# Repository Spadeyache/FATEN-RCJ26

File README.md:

# RoboCupJunior Rescue Line — Robot

Key features we have. PostTrainingQuantization(PTQ) with results simulated on the K230D chip, half-duplex serial driver with 74HCT126, asymmetric PID dependent on the IMU, custom touch sensors, and an IR camera used on the hardware.

Firmware, vision, AI training pipeline, and electronics for team **FATEN**'s [RoboCupJunior Rescue Line](https://junior.robocup.org/rescue/) robot. The robot follows a line course, handles gaps, obstacles, and intersections, then enters an evacuation zone where it detects, grabs, and carries victims using an onboard YOLO(formerly MobileNet-SSD-v2-Lite) model.

**🌐 Team website:** [faten-1tdj.vercel.app](https://faten-1tdj.vercel.app/en/index.html)

<!-- TODO: add a photo of the robot here

-->

## How the robot works

One microcontroller drives the robot; two smart co-processors digest the camera data which the control loop stays fast and deterministic.

```mermaid
flowchart LR
    subgraph IN["Inputs — co-processors and sensors"]
        direction TB
        XIAO["📷 XIAO ESP32-S3<br/>camera vision:<br/>line, green, red, silver, gap"]
        K230["🧠 K230D Zero<br/>YOLOv8n victim/colour<br/>bounding boxes"]
        IMU["🧭 MPU6050 IMU"]
        TOF["📏 VL53L7CX ToF"]
        TCH["👆 Touch bumpers"]
    end
    subgraph T["Teensy 4.1 — the conductor"]
        direction TB
        RX["sensors/ — raw byte transport"]
        PROC["processing/ — decode · filter · fuse"]
        SM["state_machine/ — pick a behaviour"]
        ACT["actions/ — PID, turn, forward, arm"]
        RX --> PROC --> SM --> ACT
    end
    subgraph OUT["Outputs"]
        direction TB
        MOT["⚙️ 4× STS3032 wheels"]
        ARM["🦾 KRS arm / gripper"]
    end
    XIAO -- "UART @ 4 Mbps" --> RX
    K230 -- "UART @ 115200" --> RX
    IMU -- "I²C" --> RX
    TOF -- "I²C" --> RX
    TCH -- "GPIO" --> RX
    ACT -- "STS bus @ 1 Mbps" --> MOT
    ACT -- "ICS bus" --> ARM
```

The Teensy firmware is a 5-layer architecture (`drivers → sensors → processing → state_machine/actions`) where calls only flow downward, with one file pair per state-machine state (`LINE_Follow`, `LINE_Gap`, `LINE_Obstacle`, `EVAC_Entry`, `EVAC_SearchDeploy`, `EVAC_Exit`, …). See [teensy/STS-imuMerge/README.md](teensy/STS-imuMerge/README.md) and the interactive [system map](Docs/architecture.html) for the full picture.

## Hardware

| Part | Role |
|---|---|
| Teensy 4.1 | Main controller: sensor fusion, state machine, motion control |
| Seeed XIAO ESP32-S3 Sense | Line-camera co-processor: line position, green/red markers, silver tape, gap detection |
| Sipeed CanMV K230D Zero | AI co-processor: YOLOv8n victim / colour detection (kmodel via nncase) |
| MPU6050 | IMU — pitch / roll / yaw |
| Pololu VL53L7CX | Multizone ToF — walls and obstacle distance |
| 4× Feetech STS3032 | Serial-bus wheel servos (1 Mbps) |
| Kondo KRS servos & Hitech HS45HB | Victim arm and grippers |
| Custom PCBs (EasyEDA) | Power distribution, adapters, breakouts — see [electronics/](electronics/) |

The custom PCBs form a stacked electronics module. The map below shows how the boards connect:

## Repository layout

| Directory | Contents |
|---|---|
| [teensy/](teensy/) | Teensy 4.1 firmware. **`STS-imuMerge/` is the competition firmware**; other folders are hardware bring-up tests (IMU, STS servos, touch) |
| [xiaoesp/](xiaoesp/) | XIAO ESP32-S3 camera firmware (`XIAOdev/`) + Web Serial debug viewer (`esp32_camera_viewer.html`) |
| [k230-final-train/](k230-final-train/) | **Current** YOLOv8n training pipeline: dataset → train → ONNX → kmodel → simulate → compare → deploy, all in Docker, one script per step |
| [k230-inference/](k230-inference/) | MicroPython code that runs on the K230D (CanMV): live detection, UART protocol to the Teensy |
| [k230/](k230/) | Legacy training pipeline + datasets (superseded by `k230-final-train/`) |
| [electronics/](electronics/) | EasyEDA projects, 3D exports, KiCad archive |
| [Docs/](Docs/) | Interactive HTML docs — open in a browser (see below) |
| [dev-tools/](dev-tools/) | Flashing images, servo manager, drivers, terminal tools |

## Documentation

The `Docs/` folder holds self-contained HTML documents (open locally in any browser):

- [architecture.html](Docs/architecture.html) — full system map: co-processors, 5-layer firmware, state machine, PID
- [APIs.html](Docs/APIs.html) — inter-board protocols and APIs
- [mapping-overview.html](Docs/mapping-overview.html) — mapping / pose overview
- [hardware530_design_upgrade.html](Docs/hardware530_design_upgrade.html), [hardware530_parts_upgrade.html](Docs/hardware530_parts_upgrade.html) — hardware upgrade notes
- [k526_PTQ_model_compare.html](Docs/k526_PTQ_model_compare.html) — kmodel post-training-quantization comparison

Each firmware layer also documents itself: every `src/<layer>/` folder has its own `README.md` with that layer's rules.

## Building and running

### Teensy firmware

Requires [Teensyduino](https://www.pjrc.com/teensy/teensyduino.html) (Arduino IDE or `arduino-cli` with the `teensy:avr` core):

```powershell
cd teensy/STS-imuMerge
arduino-cli compile --fqbn "teensy:avr:teensy41:usb=serial,speed=600,opt=o2std,keys=en-us" --build-path build .
```

### XIAO camera firmware

Build profile is pinned in [sketch.yaml](xiaoesp/XIAOdev/sketch.yaml) (esp32 core 3.3.7):

```powershell
cd xiaoesp/XIAOdev
arduino-cli compile --profile xiaoesp32s3
```

### K230D AI co-processor

1. Flash the CanMV MicroPython image (`CanMV_K230D_Zero_micropython_v1.5-legacy … nncase_v2.9.0`, in [dev-tools/](dev-tools/)) — see [k230-inference/README.md](k230-inference/README.md)
2. Copy the contents of [k230-inference/](k230-inference/) plus your `.kmodel` to the device SD card

### Training a new model

Fully reproducible in Docker — annotated dataset in, deployable `.kmodel` out:

```powershell
cd k230-final-train
.\competition_run.ps1 -Name victim_v2 -Epochs 100
```

See [k230-final-train/README.md](k230-final-train/README.md) for the step-by-step scripts and the PTQ search/compare workflow. Note: kmodels must be converted with **nncase 2.9.0-compatible tooling** to match the flashed CanMV firmware.

## Acknowledgements

### Sponsors

Team FATEN thanks the sponsors who made this robot possible:

<p>
  &nbsp;&nbsp;&nbsp;
  &nbsp;&nbsp;&nbsp;
  &nbsp;&nbsp;&nbsp;
  &nbsp;&nbsp;&nbsp;
  
</p>

- **[EasyEDA](https://easyeda.com/) & [JLCPCB](https://jlcpcb.com/)** — provided the PCB design software and board fabrication credit; the integrated design-to-manufacture workflow carried our boards smoothly from schematic to delivered PCB.
- **[Keeppower](https://keeppower.com/)** — supplied high-spec protected batteries, with the protection circuit custom-designed for our robot, and covered most of the battery and shipping costs.
- **[Hitec](https://hitecrcd.com/)** — provided motors for the robot arm along with battery chargers and maintenance jigs; their high-spec LiFePO4 balance charger kept our batteries reliably charged throughout the competition.
- **[Pololu](https://www.pololu.com/)** — supported the team's sensor hardware, including the VL53L7CX multizone time-of-flight sensor the robot uses for wall and obstacle detection.

More photos from the competition are in our [Google Drive folder](https://drive.google.com/drive/folders/1ek6edaTA_Ugfu6BttLYHi5sbRvwh5g2C).

### Institutions

Our team members represent:

<p>
  &nbsp;&nbsp;&nbsp;
  &nbsp;&nbsp;&nbsp;
  
</p>

### Open source

This robot builds on Ultralytics YOLOv8, nncase, CanMV, Teensyduino, and the Arduino ESP32 core.

## License

This project is licensed under the **Creative Commons Attribution-NonCommercial 4.0 International License (CC BY-NC 4.0)** see [LICENSE](LICENSE) for details.

In short: you're welcome to study this project, learn from it, and build your own work on top of it, as long as you credit team FATEN (a link back to this repository) and don't use it for commercial purposes. Please don't just lift the code wholesale.

Third-party components (YOLOv8, nncase, CanMV, Teensyduino, the Arduino ESP32 core, etc.) remain under their own licenses.

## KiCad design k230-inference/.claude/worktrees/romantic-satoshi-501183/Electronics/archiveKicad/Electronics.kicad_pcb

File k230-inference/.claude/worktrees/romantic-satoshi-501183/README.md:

/CanMV... for k230d zero development

/k230dev-yolo...enviroment to train a yolov8n model and convert to a .kmodel for k230

/teensydev... teensy4.1 developments

/xiaoesp32dev...all developments for xiao

/Electronics... all electronics development - We use EasyEDA as our main ecad software

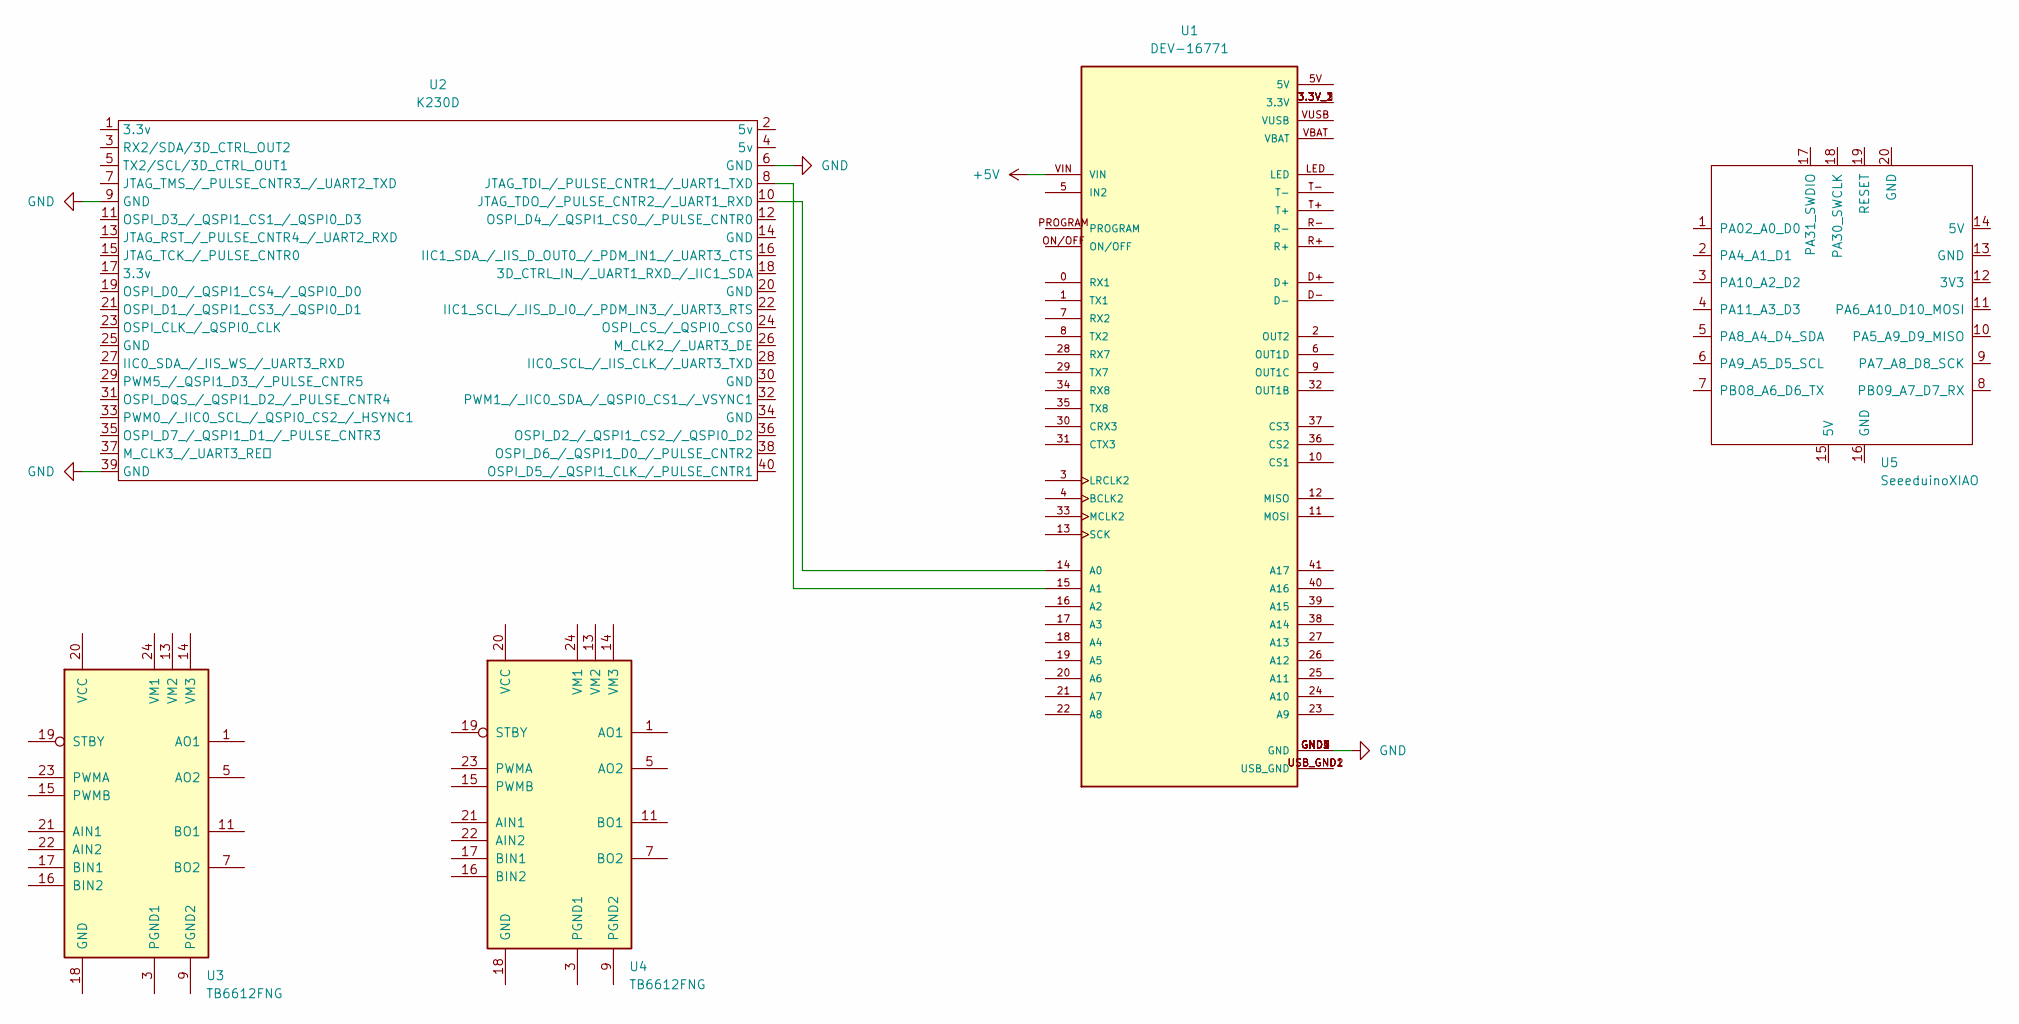
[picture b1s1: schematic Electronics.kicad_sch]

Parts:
U1: DEV-16771; MODULE_DEV-16771; PARTREV 4.1
U2: K230D; PinSocket_2x20_P2.54mm_Vertical_SMD
U3, U4: TB6612FNG; SSOP-24_5.3x8.2mm_P0.65mm
U5: SeeeduinoXIAO; MCU_Seeed_ESP32C3

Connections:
+5V: U1.VIN
GND: U1.GND1 (GND), U1.GND2 (GND), U1.GND3 (GND), U1.GND4 (GND), U1.GND5 (GND), U2.6 (GND), U2.9 (GND), U2.39 (GND)
unnamed: U1.3.3V_1 (3.3V), U1.3.3V_2 (3.3V), U1.3.3V_3 (3.3V)
unnamed: U1.14 (A0), U2.10 (JTAG_TDO_/_PULSE_CNTR2_/_UART1_RXD)
unnamed: U1.15 (A1), U2.8 (JTAG_TDI_/_PULSE_CNTR1_/_UART1_TXD)
unnamed: U1.USB_GND1 (USB_GND), U1.USB_GND2 (USB_GND)
unnamed: U3.1 (AO1), U3.2 (AO1)
unnamed: U3.5 (AO2), U3.6 (AO2)
unnamed: U3.11 (BO1), U3.12 (BO1)
unnamed: U3.7 (BO2), U3.8 (BO2)
unnamed: U3.3 (PGND1), U3.4 (PGND1)
unnamed: U3.9 (PGND2), U3.10 (PGND2)
unnamed: U4.1 (AO1), U4.2 (AO1)
unnamed: U4.5 (AO2), U4.6 (AO2)
unnamed: U4.11 (BO1), U4.12 (BO1)
unnamed: U4.7 (BO2), U4.8 (BO2)
unnamed: U4.3 (PGND1), U4.4 (PGND1)
unnamed: U4.9 (PGND2), U4.10 (PGND2)

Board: 2 copper layers, 5 parts (0 on the bottom side), 17 nets, no tracks yet.

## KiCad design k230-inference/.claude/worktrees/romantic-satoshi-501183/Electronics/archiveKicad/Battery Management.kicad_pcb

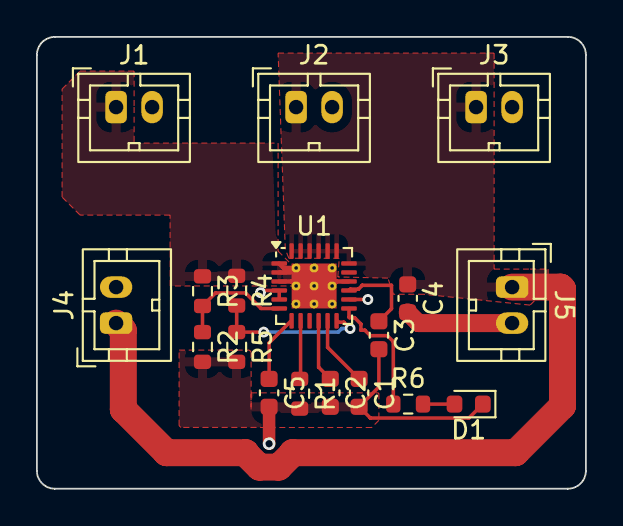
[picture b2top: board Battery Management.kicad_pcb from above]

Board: 2 copper layers, 30.5 x 25.1 mm, 18 parts (0 on the bottom side), 12 nets.

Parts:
C1: 330pF; C_0603_1608Metric
C2: 128pF; C_0603_1608Metric
C3: 2.2nF; C_0603_1608Metric
C4: 470nF; C_0603_1608Metric
C5: 22nF; C_0603_1608Metric
D1: LED; D_0603_1608Metric
J1, J2, J3, J4, J5: Conn_01x02; TE_440054-2_1x02_P2.00mm_Vertical
R1: 148; R_0603_1608Metric
R2: 225k; R_0603_1608Metric
R3, R4: 1M; R_0603_1608Metric
R5: 2k; R_0603_1608Metric
R6: 10K; R_0603_1608Metric
U1: TSP25983; VQFN-24-1EP_4x4mm_P0.5mm_EP2.5x2.5mm_ThermalVias

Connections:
+6.6V: C4.1, J2.1, J3.1, J4.1, J5.1, U1.17 (OUT_2), U1.18 (OUT_3), U1.19 (OUT_4), U1.20 (OUT_5), U1.21 (OUT_6), U1.22 (OUT_7), U1.23 (OUT_8), U1.24 (OUT)
+BATT: J1.1, R3.1, R4.1, U1.1 (IN_2), U1.2 (IN_3), U1.3 (IN_4), U1.16 (IN_5), U1.25 (IN)
GND: C1.2, C2.2, C3.2, C4.2, C5.2, D1.1 (K), J1.2, J2.2, J3.2, J4.2, J5.2, R1.2, R2.2, R5.2, U1.4 (GND_2), U1.5 (GND_3), U1.14 (GND_4)
unnamed: D1.2 (A), R6.2
unnamed: C3.1, U1.15 (DV/DT_BGATE)
unnamed: R2.1, R3.2, U1.6 (EN/UVLO)
unnamed: R1.1, U1.8 (ILIM)
unnamed: C5.1, U1.7 (ITIMER)
unnamed: C1.1, U1.11 (NRETRY)
unnamed: R4.2, R5.1, U1.12 (OVLO)
unnamed: R6.1, U1.13 (PG)
unnamed: C2.1, U1.10 (RETRY_DLY)

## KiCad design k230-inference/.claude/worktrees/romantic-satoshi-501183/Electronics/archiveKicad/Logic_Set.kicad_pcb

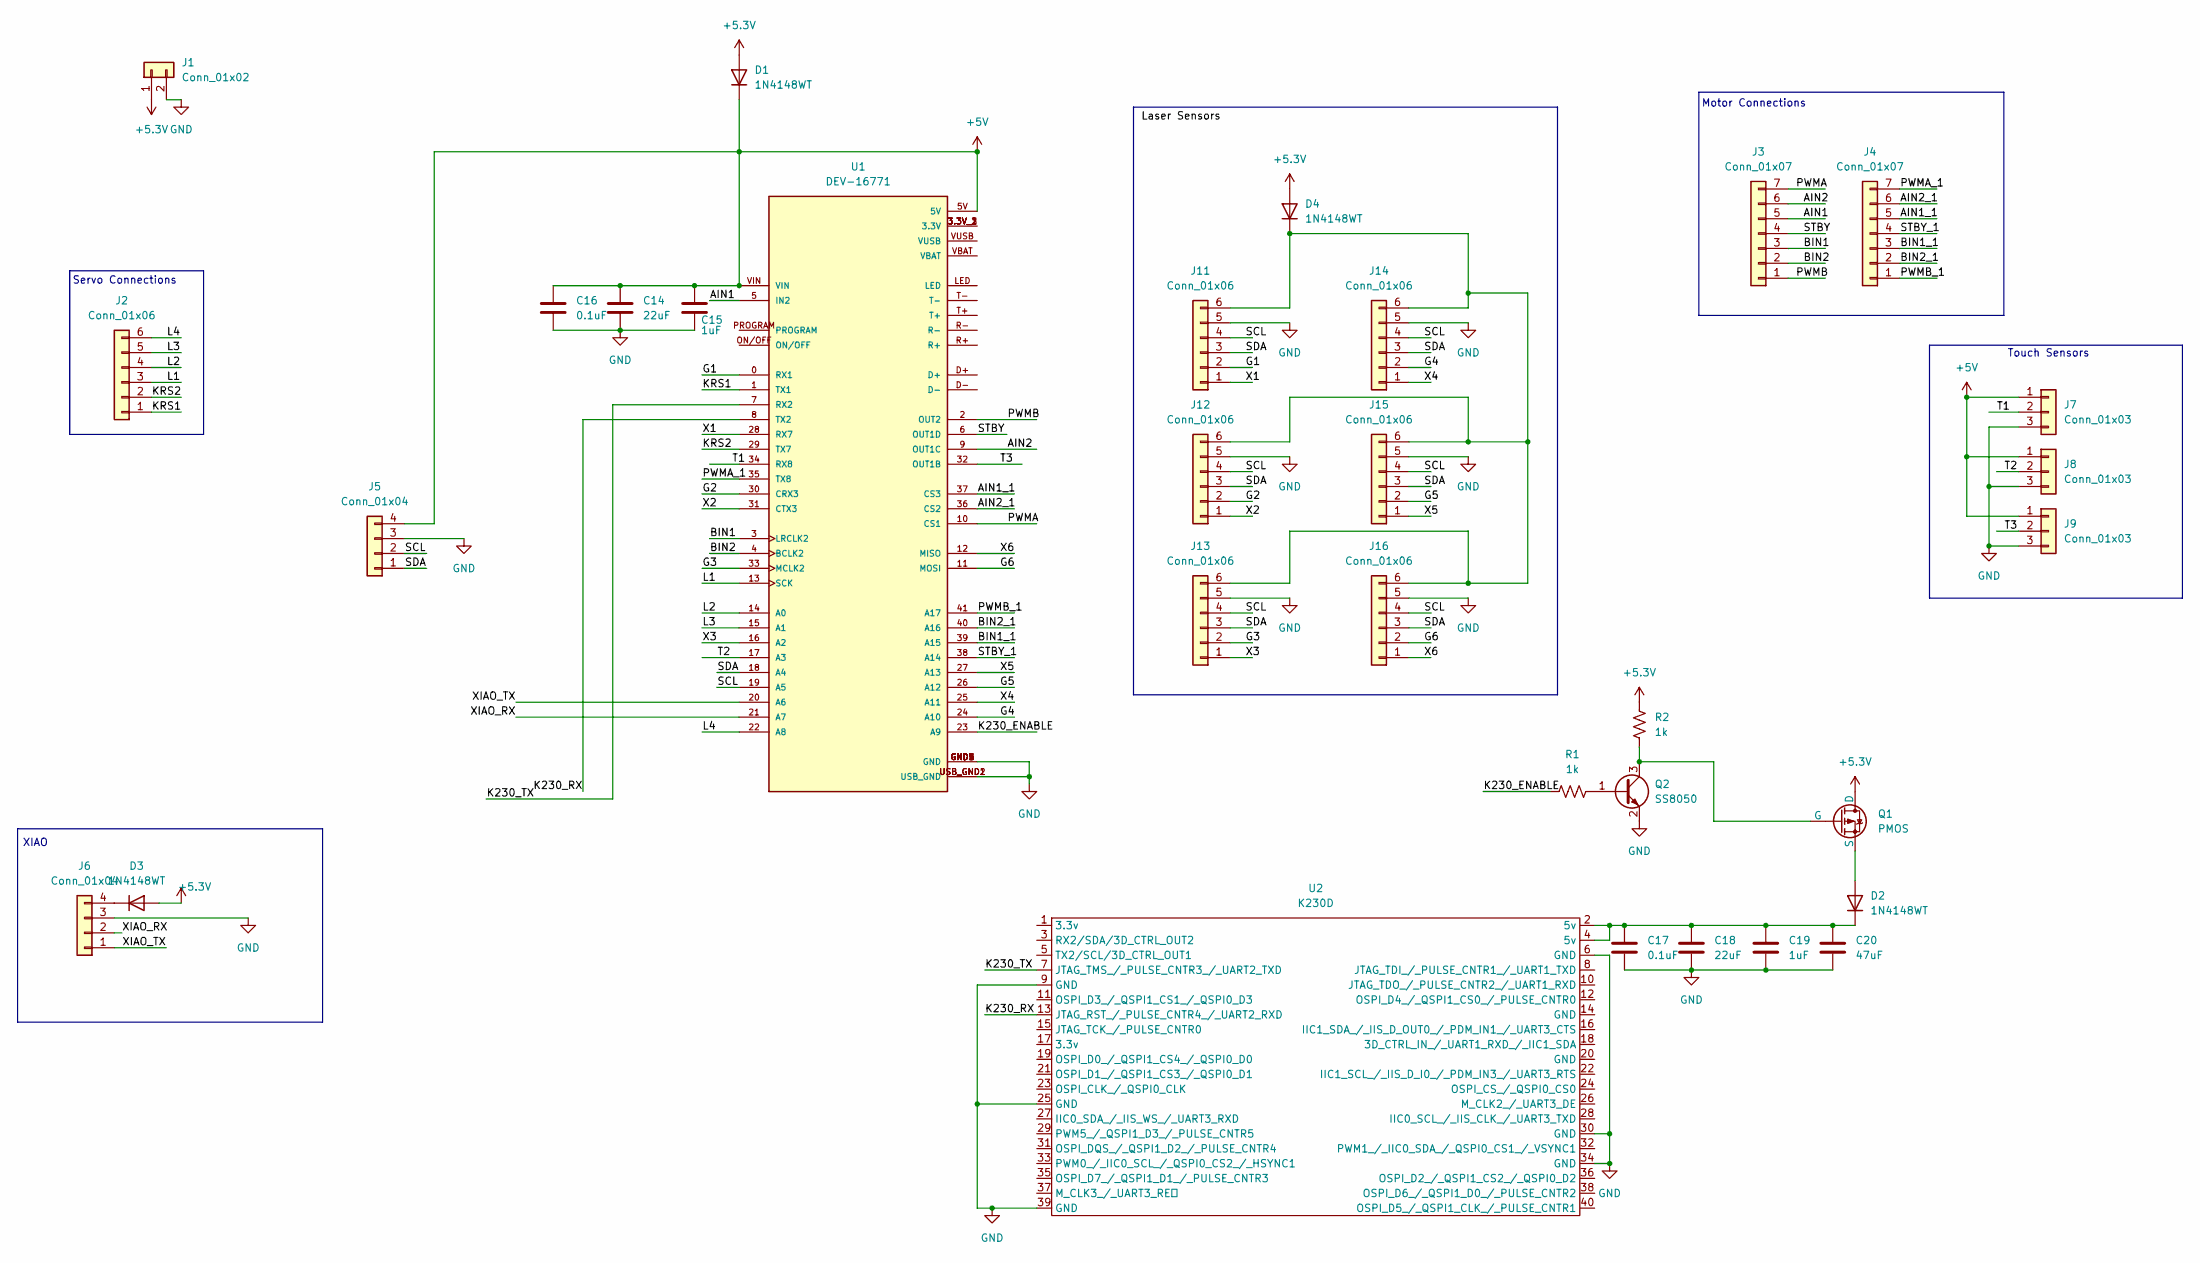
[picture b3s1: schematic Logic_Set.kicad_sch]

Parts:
C14, C18: 22uF; C_0603_1608Metric
C15, C19: 1uF; C_0603_1608Metric
C16, C17: 0.1uF; C_0603_1608Metric
C20: 47uF; C_0603_1608Metric
D1, D2, D3, D4: 1N4148WT; D_SOD-523
J1: Conn_01x02; Molex_KK-396_5273-02A_1x02_P3.96mm_Vertical
J2, J11, J12, J13, J14, J15, J16: Conn_01x06; JST_EH_B6B-EH-A_1x06_P2.50mm_Vertical
J3, J4: Conn_01x07; JST_EH_B7B-EH-A_1x07_P2.50mm_Vertical
J5, J6: Conn_01x04; JST_EH_B4B-EH-A_1x04_P2.50mm_Vertical
J7, J8, J9: Conn_01x03; JST_EH_B3B-EH-A_1x03_P2.50mm_Vertical
Q1: PMOS; SOT-23
Q2: SS8050; SOT-23
R1, R2: 1k; R_0603_1608Metric
U1: DEV-16771; Teensy4.1; PARTREV 4.1
U2: K230D; PinSocket_2x20_P2.54mm_Vertical_SMD

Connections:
+5.3V: D1.2 (A), D3.2 (A), D4.2 (A), J1.1, Q1.1 (D), R2.1
+5V: C14.1, C15.1, C16.1, D1.1 (K), J5.4, J7.1, J8.1, J9.1, U1.5V, U1.VIN
/AIN1: J3.5, U1.5 (IN2)
/AIN1_1: J4.5, U1.37 (CS3)
/AIN2: J3.6, U1.9 (OUT1C)
/AIN2_1: J4.6, U1.36 (CS2)
/BIN1: J3.3, U1.3 (LRCLK2)
/BIN1_1: J4.3, U1.39 (A15)
/BIN2: J3.2, U1.4 (BCLK2)
/BIN2_1: J4.2, U1.40 (A16)
/G1: J11.2, U1.0 (RX1)
/G2: J12.2, U1.30 (CRX3)
/G3: J13.2, U1.33 (MCLK2)
/G4: J14.2, U1.24 (A10)
/G5: J15.2, U1.26 (A12)
/G6: J16.2, U1.11 (MOSI)
/K230_ENABLE: R1.1, U1.23 (A9)
/K230_RX: U1.8 (TX2), U2.13 (JTAG_RST_/_PULSE_CNTR4_/_UART2_RXD)
/K230_TX: U1.7 (RX2), U2.7 (JTAG_TMS_/_PULSE_CNTR3_/_UART2_TXD)
/KRS1: J2.1, U1.1 (TX1)
/KRS2: J2.2, U1.29 (TX7)
/L1: J2.3, U1.13 (SCK)
/L2: J2.4, U1.14 (A0)
/L3: J2.5, U1.15 (A1)
/L4: J2.6, U1.22 (A8)
/PWMA: J3.7, U1.10 (CS1)
/PWMA_1: J4.7, U1.35 (TX8)
/PWMB: J3.1, U1.2 (OUT2)
/PWMB_1: J4.1, U1.41 (A17)
/SCL: J5.2, J11.4, J12.4, J13.4, J14.4, J15.4, J16.4, U1.19 (A5)
/SDA: J5.1, J11.3, J12.3, J13.3, J14.3, J15.3, J16.3, U1.18 (A4)
/STBY: J3.4, U1.6 (OUT1D)
/STBY_1: J4.4, U1.38 (A14)
/T1: J7.2, U1.34 (RX8)
/T2: J8.2, U1.17 (A3)
/T3: J9.2, U1.32 (OUT1B)
/X1: J11.1, U1.28 (RX7)
/X2: J12.1, U1.31 (CTX3)
/X3: J13.1, U1.16 (A2)
/X4: J14.1, U1.25 (A11)
/X5: J15.1, U1.27 (A13)
/X6: J16.1, U1.12 (MISO)
/XIAO_RX: J6.2, U1.21 (A7)
/XIAO_TX: J6.1, U1.20 (A6)
GND: C14.2, C15.2, C16.2, C17.2, C18.2, C19.2, C20.2, J1.2, J5.3, J6.3, J7.3, J8.3, J9.3, J11.5, J12.5, J13.5, J14.5, J15.5, J16.5, Q2.2 (E), U1.GND1 (GND), U1.GND2 (GND), U1.GND3 (GND), U1.GND4 (GND), U1.GND5 (GND), U1.USB_GND1 (USB_GND), U1.USB_GND2 (USB_GND), U2.6 (GND), U2.9 (GND), U2.25 (GND), U2.30 (GND), U2.34 (GND), U2.39 (GND)
unnamed: D2.2 (A), Q1.3 (S)
unnamed: C17.1, C18.1, C19.1, C20.1, D2.1 (K), U2.2 (5v), U2.4 (5v)
unnamed: D3.1 (K), J6.4
unnamed: D4.1 (K), J11.6, J12.6, J13.6, J14.6, J15.6, J16.6
unnamed: Q1.2 (G), Q2.3 (C), R2.2
unnamed: Q2.1 (B), R1.2
unnamed: U1.3.3V_1 (3.3V), U1.3.3V_2 (3.3V), U1.3.3V_3 (3.3V)

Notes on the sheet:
Motor Connections
Servo Connections
XIAO
Touch Sensors

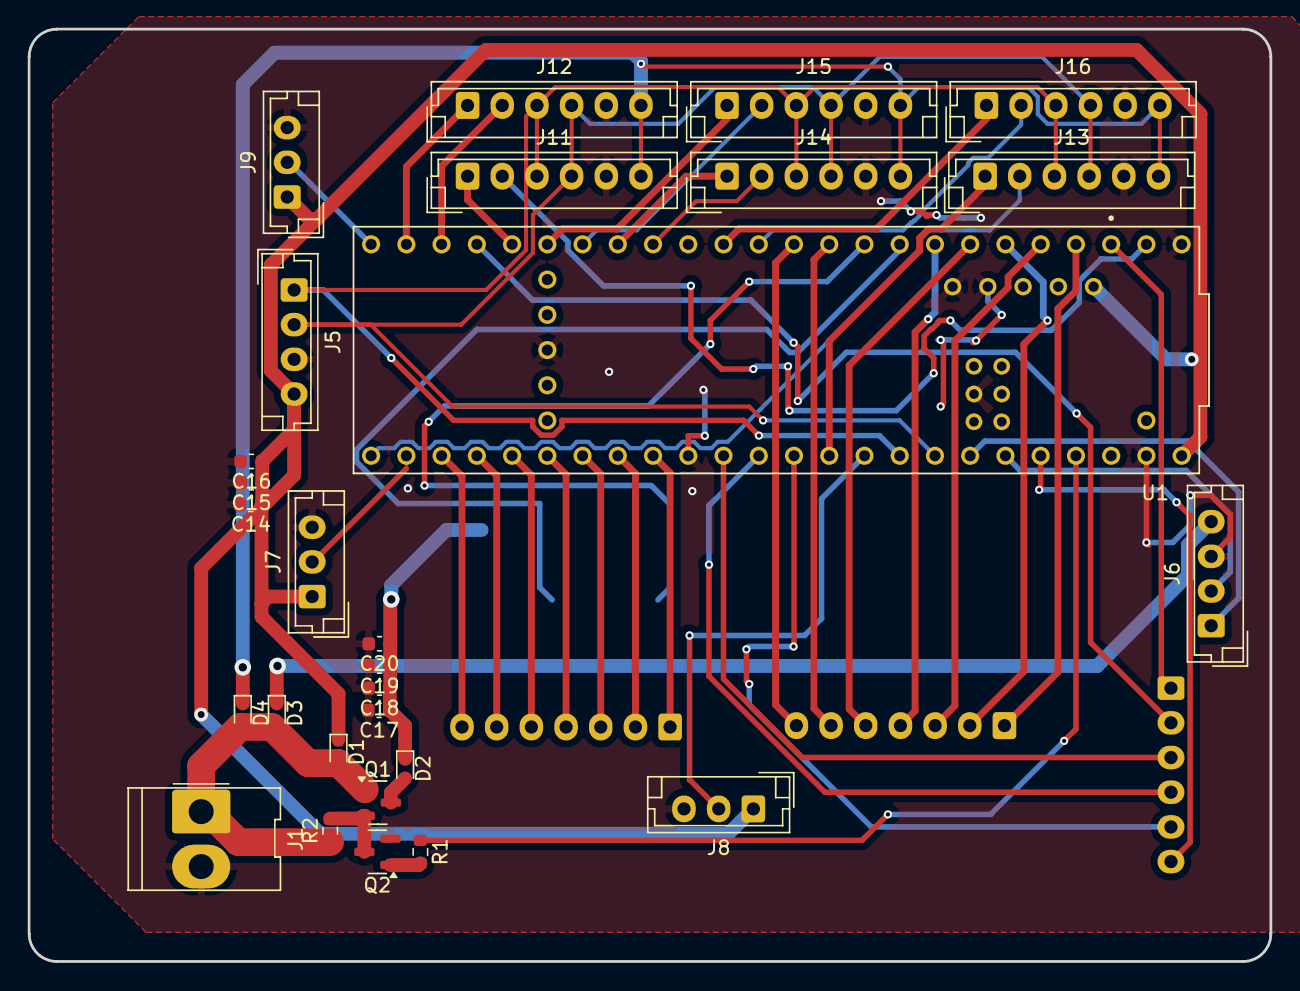
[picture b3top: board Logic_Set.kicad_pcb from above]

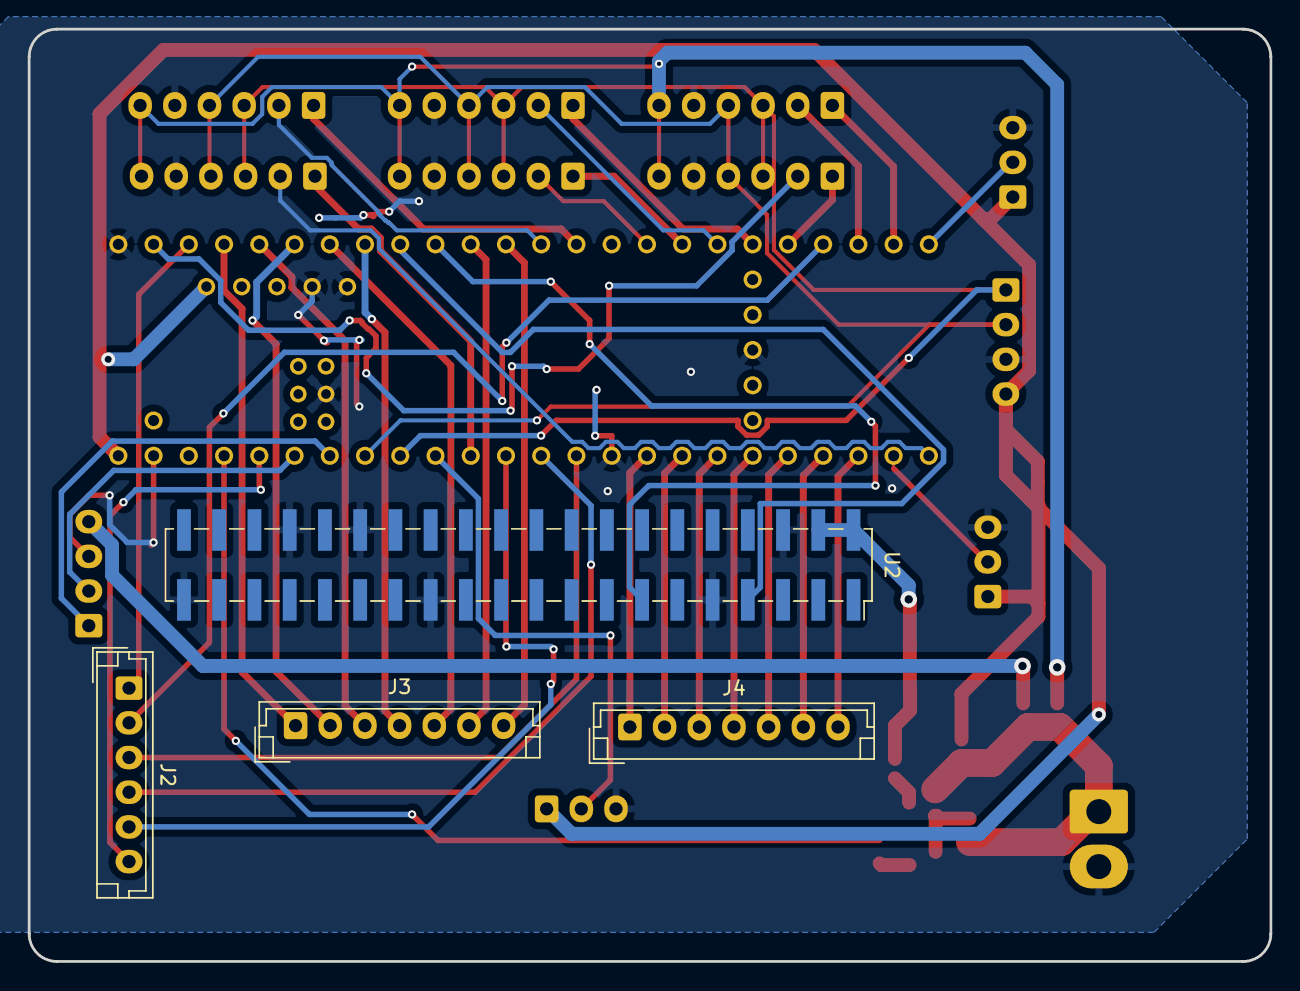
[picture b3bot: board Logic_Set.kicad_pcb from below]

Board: 2 copper layers, 89.5 x 67.2 mm, 32 parts (4 on the bottom side), 52 nets.

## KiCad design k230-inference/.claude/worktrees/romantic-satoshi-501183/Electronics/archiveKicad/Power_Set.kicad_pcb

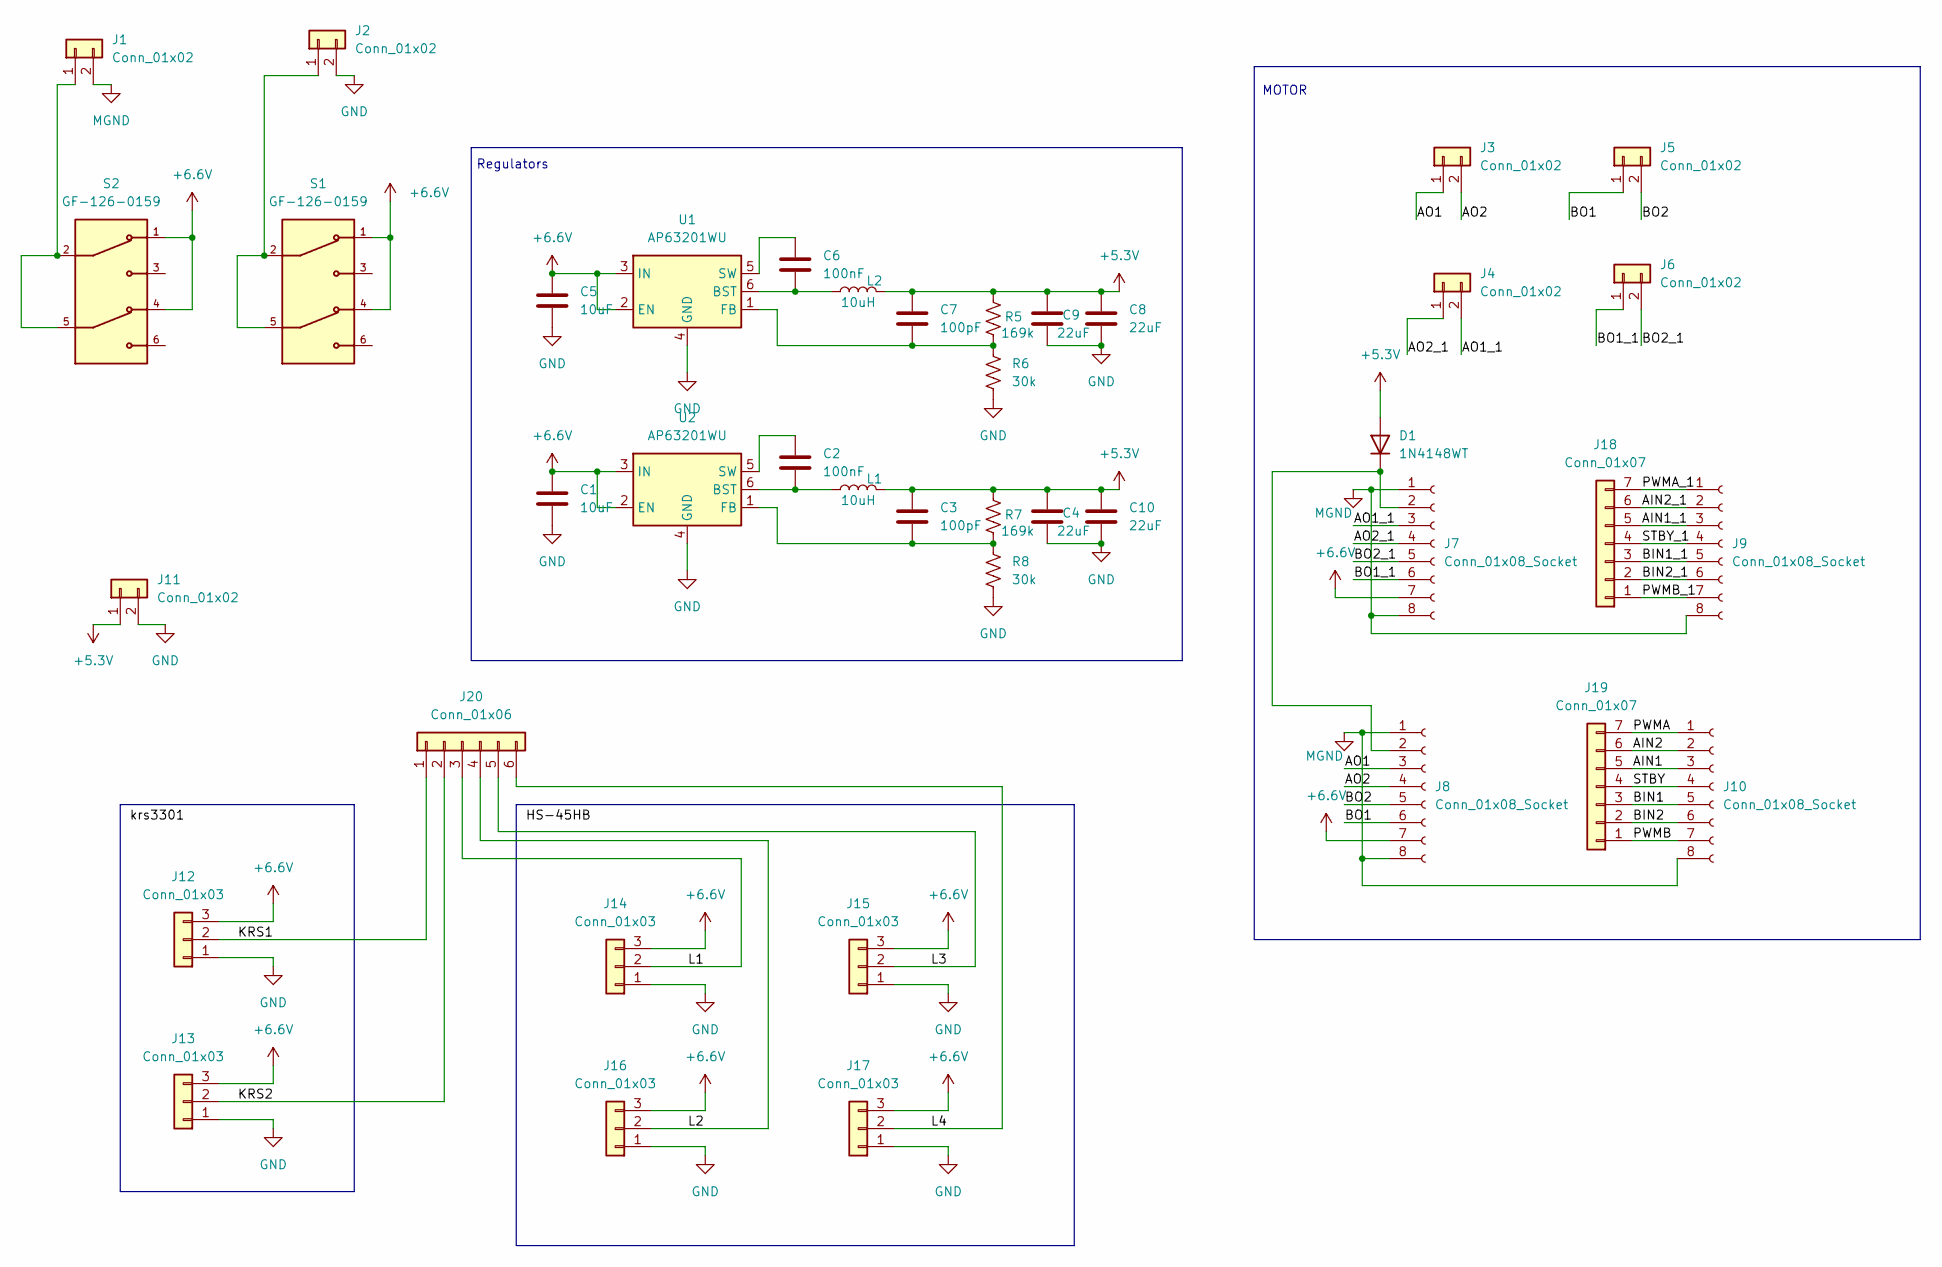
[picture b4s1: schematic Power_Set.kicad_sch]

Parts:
C1, C5: 10uF; C_0603_1608Metric
C2, C6: 100nF; C_0603_1608Metric
C3, C7: 100pF; C_0603_1608Metric
C4, C8, C9, C10: 22uF; C_0603_1608Metric
D1: 1N4148WT; D_SOD-523
J1, J2, J3, J4, J5, J6, J11: Conn_01x02; Molex_KK-396_A-41791-0002_1x02_P3.96mm_Vertical
J7, J8, J9, J10: Conn_01x08_Socket; PinHeader_1x08_P2.54mm_Vertical
J12, J13, J14, J15, J16, J17: Conn_01x03; JST_EH_B3B-EH-A_1x03_P2.50mm_Vertical
J18, J19: Conn_01x07; JST_EH_B7B-EH-A_1x07_P2.50mm_Vertical
J20: Conn_01x06; JST_EH_B6B-EH-A_1x06_P2.50mm_Vertical
L1, L2: 10uH; L_1210_3225Metric
R5, R7: 169k; R_0603_1608Metric
R6, R8: 30k; R_0603_1608Metric
S1, S2: GF-126-0159; SW_GF-126-0159
U1, U2: AP63201WU; TSOT-23-6

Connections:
+5.3V: C3.1, C4.1, C7.1, C8.1, C9.1, C10.1, D1.2 (A), J11.1, L1.2, L2.2, R5.1, R7.1
+6.6V: C1.1, C5.1, J7.7, J8.7, J12.3, J13.3, J14.3, J15.3, J16.3, J17.3, S1.1, S1.4, S2.1, S2.4, U1.2 (EN), U1.3 (IN), U2.2 (EN), U2.3 (IN)
/AIN1: J10.3, J19.5
/AIN1_1: J9.3, J18.5
/AIN2: J10.2, J19.6
/AIN2_1: J9.2, J18.6
/AO1: J3.1, J8.3
/AO1_1: J4.2, J7.3
/AO2: J3.2, J8.4
/AO2_1: J4.1, J7.4
/BIN1: J10.5, J19.3
/BIN1_1: J9.5, J18.3
/BIN2: J10.6, J19.2
/BIN2_1: J9.6, J18.2
/BO1: J5.1, J8.6
/BO1_1: J6.1, J7.6
/BO2: J5.2, J8.5
/BO2_1: J6.2, J7.5
/KRS1: J12.2, J20.1
/KRS2: J13.2, J20.2
/L1: J14.2, J20.3
/L2: J16.2, J20.4
/L3: J15.2, J20.5
/L4: J17.2, J20.6
/PWMA: J10.1, J19.7
/PWMA_1: J9.1, J18.7
/PWMB: J10.7, J19.1
/PWMB_1: J9.7, J18.1
/STBY: J10.4, J19.4
/STBY_1: J9.4, J18.4
GND: C1.2, C4.2, C5.2, C8.2, C9.2, C10.2, J2.2, J11.2, J12.1, J13.1, J14.1, J15.1, J16.1, J17.1, R6.2, R8.2, U1.4 (GND), U2.4 (GND)
MGND: J1.2, J7.1, J7.8, J8.1, J8.8, J9.8, J10.8
unnamed: D1.1 (K), J7.2, J8.2
unnamed: J1.1, S2.2, S2.5
unnamed: J2.1, S1.2, S1.5
unnamed: C6.2, L2.1, U1.6 (BST)
unnamed: C7.2, R5.2, R6.1, U1.1 (FB)
unnamed: C6.1, U1.5 (SW)
unnamed: C2.2, L1.1, U2.6 (BST)
unnamed: C3.2, R7.2, R8.1, U2.1 (FB)
unnamed: C2.1, U2.5 (SW)

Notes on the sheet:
Regulators
MOTOR

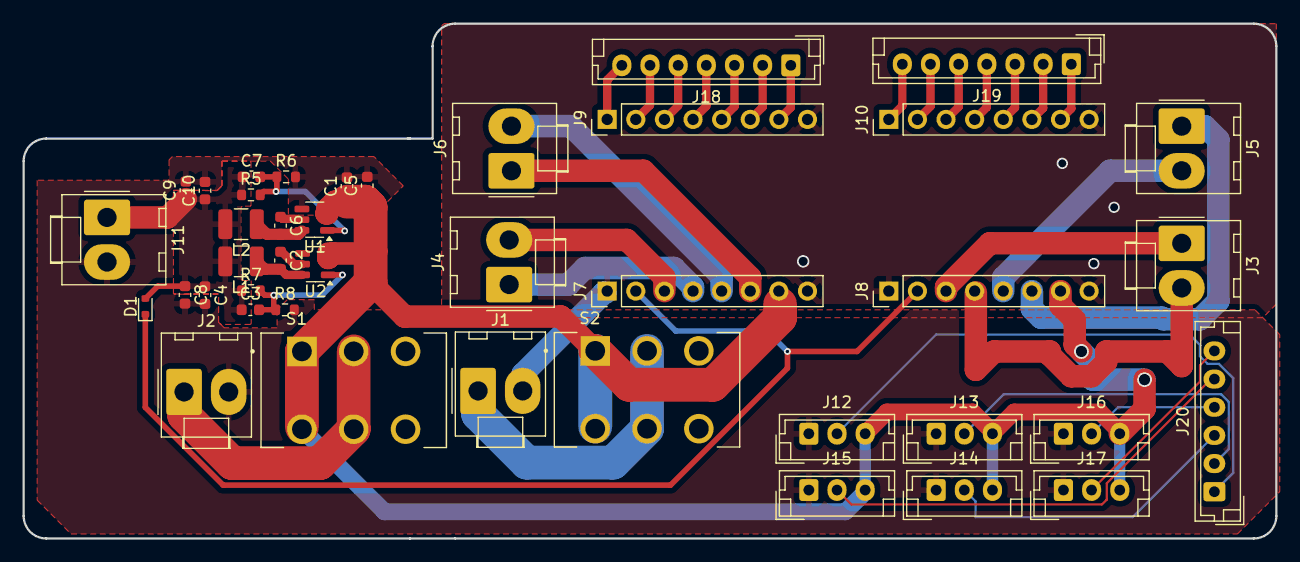
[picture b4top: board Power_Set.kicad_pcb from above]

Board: 2 copper layers, 111.2 x 45.7 mm, 41 parts (0 on the bottom side), 41 nets.

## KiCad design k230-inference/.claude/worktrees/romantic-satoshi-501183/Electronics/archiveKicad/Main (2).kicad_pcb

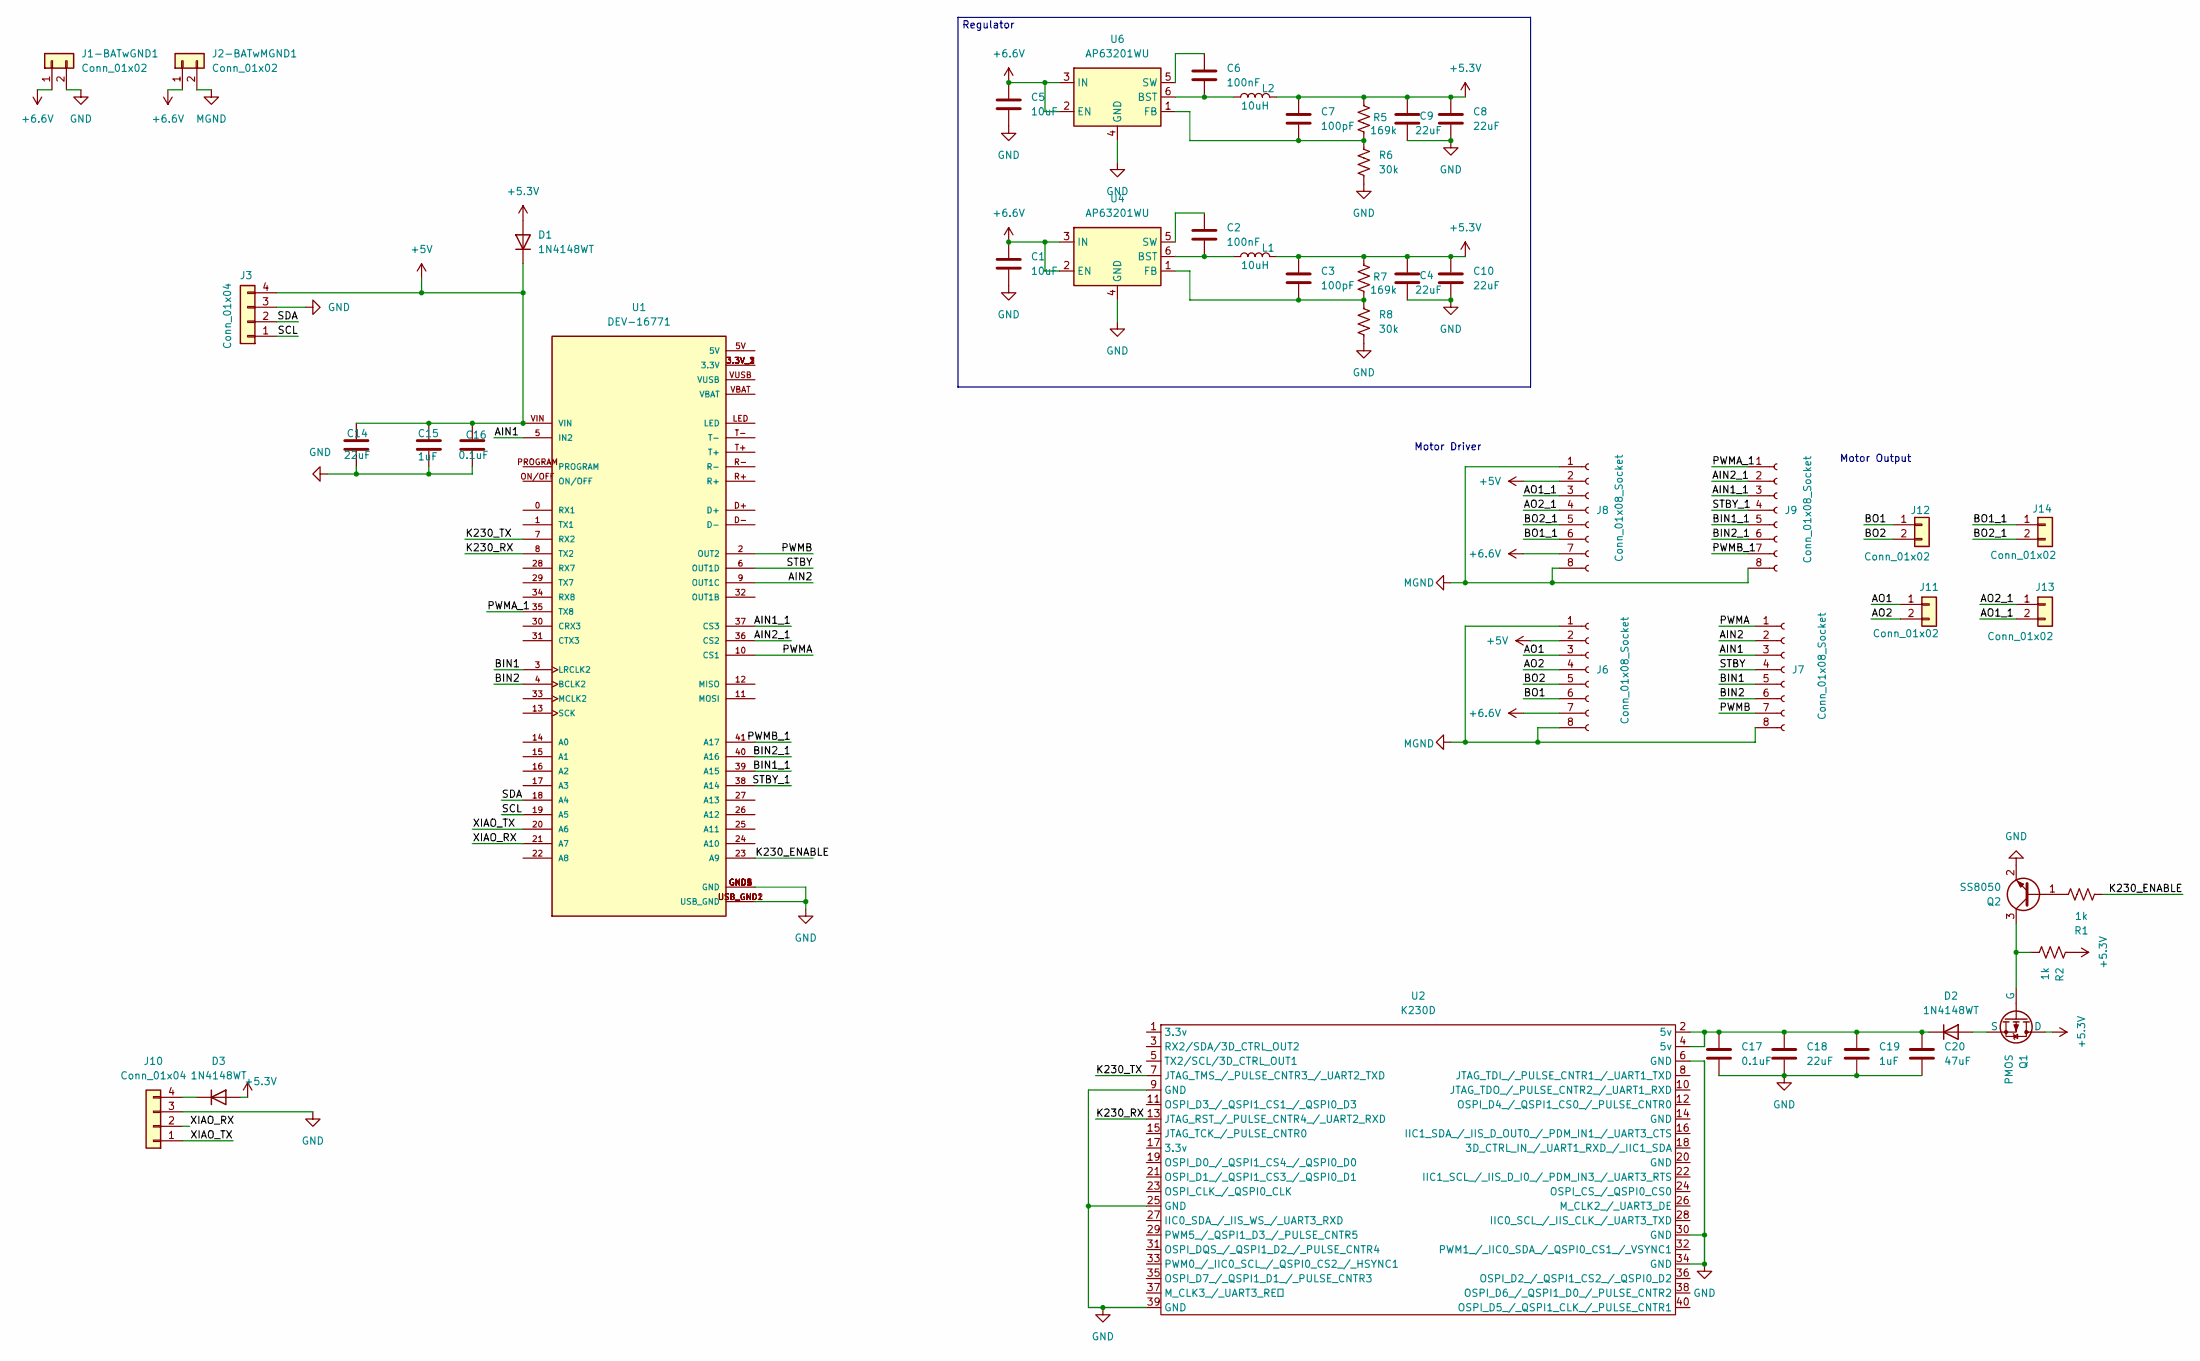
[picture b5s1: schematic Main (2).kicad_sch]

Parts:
C1, C5: 10uF; C_0603_1608Metric
C2, C6: 100nF; C_0603_1608Metric
C3, C7: 100pF; C_0603_1608Metric
C4, C8, C9, C10, C14, C18: 22uF; C_0603_1608Metric
C15, C19: 1uF; C_0603_1608Metric
C16, C17: 0.1uF; C_0603_1608Metric
C20: 47uF; C_0603_1608Metric
D1, D2, D3: 1N4148WT; D_SOD-523
J1-BATwGND1, J2-BATwMGND1, J11, J12, J13, J14: Conn_01x02; TE_440054-2_1x02_P2.00mm_Vertical
J3, J10: Conn_01x04; JST_XH_B4B-XH-A_1x04_P2.50mm_Vertical
J6, J7, J8, J9: Conn_01x08_Socket; PinHeader_1x08_P2.54mm_Vertical
L1, L2: 10uH; L_0603_1608Metric
Q1: PMOS; SOT-23
Q2: SS8050; SOT-23
R1, R2: 1k; R_0603_1608Metric
R5, R7: 169k; R_0603_1608Metric
R6, R8: 30k; R_0603_1608Metric
U1: DEV-16771; Teensy4.1; PARTREV 4.1
U2: K230D; PinSocket_2x20_P2.54mm_Vertical_SMD
U4, U6: AP63201WU; TSOT-23-6

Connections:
+5.3V: C3.1, C4.1, C7.1, C8.1, C9.1, C10.1, D1.2 (A), D3.2 (A), L1.2, L2.2, Q1.1 (D), R2.1, R5.1, R7.1; also elsewhere on the board
+5V: C14.1, C15.1, C16.1, D1.1 (K), J3.4, J6.2, J8.2, U1.VIN
+6.6V: C1.1, C5.1, J1-BATwGND1.1, J2-BATwMGND1.1, J6.7, J8.7, U4.2 (EN), U4.3 (IN), U6.2 (EN), U6.3 (IN); also elsewhere on the board
/AIN1: J7.3, U1.5 (IN2)
/AIN1_1: J9.3, U1.37 (CS3)
/AIN2: J7.2, U1.9 (OUT1C)
/AIN2_1: J9.2, U1.36 (CS2)
/AO1: J6.3, J11.1
/AO1_1: J8.3, J13.2
/AO2: J6.4, J11.2
/AO2_1: J8.4, J13.1
/BIN1: J7.5, U1.3 (LRCLK2)
/BIN1_1: J9.5, U1.39 (A15)
/BIN2: J7.6, U1.4 (BCLK2)
/BIN2_1: J9.6, U1.40 (A16)
/BO1: J6.6, J12.1
/BO1_1: J8.6, J14.1
/BO2: J6.5, J12.2
/BO2_1: J8.5, J14.2
/K230_ENABLE: R1.1, U1.23 (A9)
/K230_RX: U1.8 (TX2), U2.13 (JTAG_RST_/_PULSE_CNTR4_/_UART2_RXD)
/K230_TX: U1.7 (RX2), U2.7 (JTAG_TMS_/_PULSE_CNTR3_/_UART2_TXD)
/PWMA: J7.1, U1.10 (CS1)
/PWMA_1: J9.1, U1.35 (TX8)
/PWMB: J7.7, U1.2 (OUT2)
/PWMB_1: J9.7, U1.41 (A17)
/SCL: J3.1, U1.19 (A5)
/SDA: J3.2, U1.18 (A4)
/STBY: J7.4, U1.6 (OUT1D)
/STBY_1: J9.4, U1.38 (A14)
/XIAO_RX: J10.2, U1.21 (A7)
/XIAO_TX: J10.1, U1.20 (A6)
GND: C1.2, C4.2, C5.2, C8.2, C9.2, C10.2, C14.2, C15.2, C16.2, C17.2, C18.2, C19.2, C20.2, J1-BATwGND1.2, J3.3, J10.3, Q2.2 (E), R6.2, R8.2, U1.GND1 (GND), U1.GND2 (GND), U1.GND3 (GND), U1.GND4 (GND), U1.GND5 (GND), U1.USB_GND1 (USB_GND), U1.USB_GND2 (USB_GND), U2.6 (GND), U2.9 (GND), U2.25 (GND), U2.30 (GND), U2.34 (GND), U2.39 (GND), U4.4 (GND), U6.4 (GND); also elsewhere on the board
MGND: J2-BATwMGND1.2, J6.1, J6.8, J7.8, J8.1, J8.8, J9.8; also elsewhere on the board
unnamed: D2.2 (A), Q1.3 (S)
unnamed: C17.1, C18.1, C19.1, C20.1, D2.1 (K), U2.2 (5v), U2.4 (5v)
unnamed: D3.1 (K), J10.4
unnamed: Q1.2 (G), Q2.3 (C), R2.2
unnamed: Q2.1 (B), R1.2
unnamed: U1.3.3V_1 (3.3V), U1.3.3V_2 (3.3V), U1.3.3V_3 (3.3V)
unnamed: C2.2, L1.1, U4.6 (BST)
unnamed: C3.2, R7.2, R8.1, U4.1 (FB)
unnamed: C2.1, U4.5 (SW)
unnamed: C6.2, L2.1, U6.6 (BST)
unnamed: C7.2, R5.2, R6.1, U6.1 (FB)
unnamed: C6.1, U6.5 (SW)

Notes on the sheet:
Regulator
Motor Output
Motor Driver
